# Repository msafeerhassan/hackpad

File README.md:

# My Cool Hackpad
## Project Details
My hackpad consist of 4 keys, a 0.91" OLED Display and two SK6812-MINI LED'S. Moreover, I am using XIAO RP2040. The case will be 3D printed while the the PCB will be printed and shipped by JLCPCB. I am going to hand solder all the componenets. PCB and Schematic Diagram is designed in KiCad while the Case is designed in Fusion360.

My Schematic Diagram:

My PCB:

3D Case with PCB:

Code Screenshot:

3D Case:

## Bill of Materials

4x Switches/Buttons

2x SK6812 MINI LEDs

1x 0.91" 128x32 OLED Display

1x XIAO RP2040

3D Printed Case (2 printed parts - top and bottom case)

1x PCB from JLCPCB

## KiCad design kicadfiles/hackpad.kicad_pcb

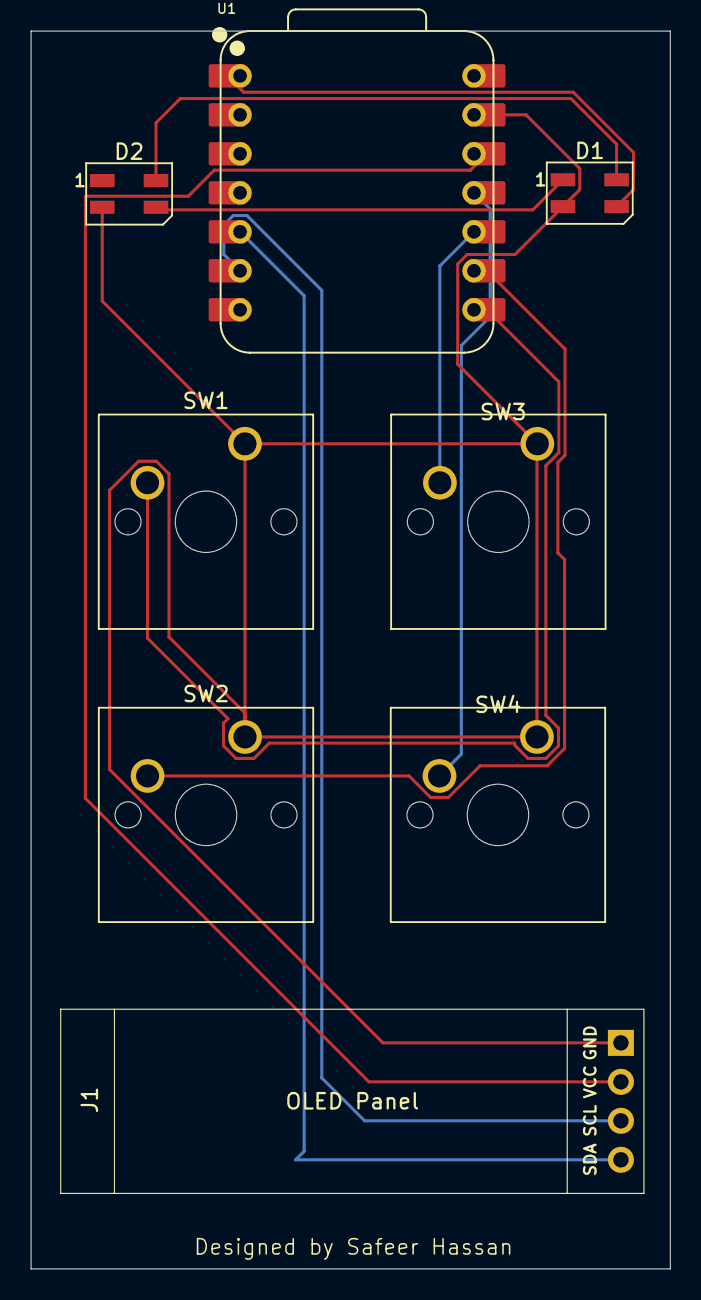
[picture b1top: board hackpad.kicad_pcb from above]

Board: 2 copper layers, 41.7 x 80.7 mm, 8 parts (0 on the bottom side), 11 nets.

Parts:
D1, D2: SK6812MINI; LED_SK6812MINI_PLCC4_3.5x3.5mm_P1.75mm
J1: 0.91" OLED Display; SSD1306-0.91-OLED-4pin-128x32
SW1, SW2, SW3, SW4: SW_Push; SW_Cherry_MX_1.00u_PCB
U1: XIAO-RP2040-DIP

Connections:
GND: D1.2 (VSS), D2.2 (VSS), J1.1 (GND), SW1.1, SW2.1, SW3.1, SW4.1, U1.13 (GND)
unnamed: D1.3 (DIN), U1.1 (GPIO26/ADC0/A0)
unnamed: D1.1 (DOUT), D2.3 (DIN)
unnamed: D1.4 (VDD), D2.4 (VDD)
unnamed: J1.3 (SCL), U1.6 (GPIO7/SCL)
unnamed: J1.4 (SDA), U1.5 (GPIO6/SDA)
unnamed: J1.2 (VCC), U1.12 (3V3)
unnamed: SW1.2, U1.8 (GPIO1/RX)
unnamed: SW2.2, U1.9 (GPIO2/SCK)
unnamed: SW4.2, U1.11 (GPIO3/MOSI)
unnamed: SW3.2, U1.10 (GPIO4/MISO)

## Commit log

2025-12-13 added cad files
2025-12-13 added kicad files
2025-12-14 code uploaded
2025-12-14 Update README with project information and images
